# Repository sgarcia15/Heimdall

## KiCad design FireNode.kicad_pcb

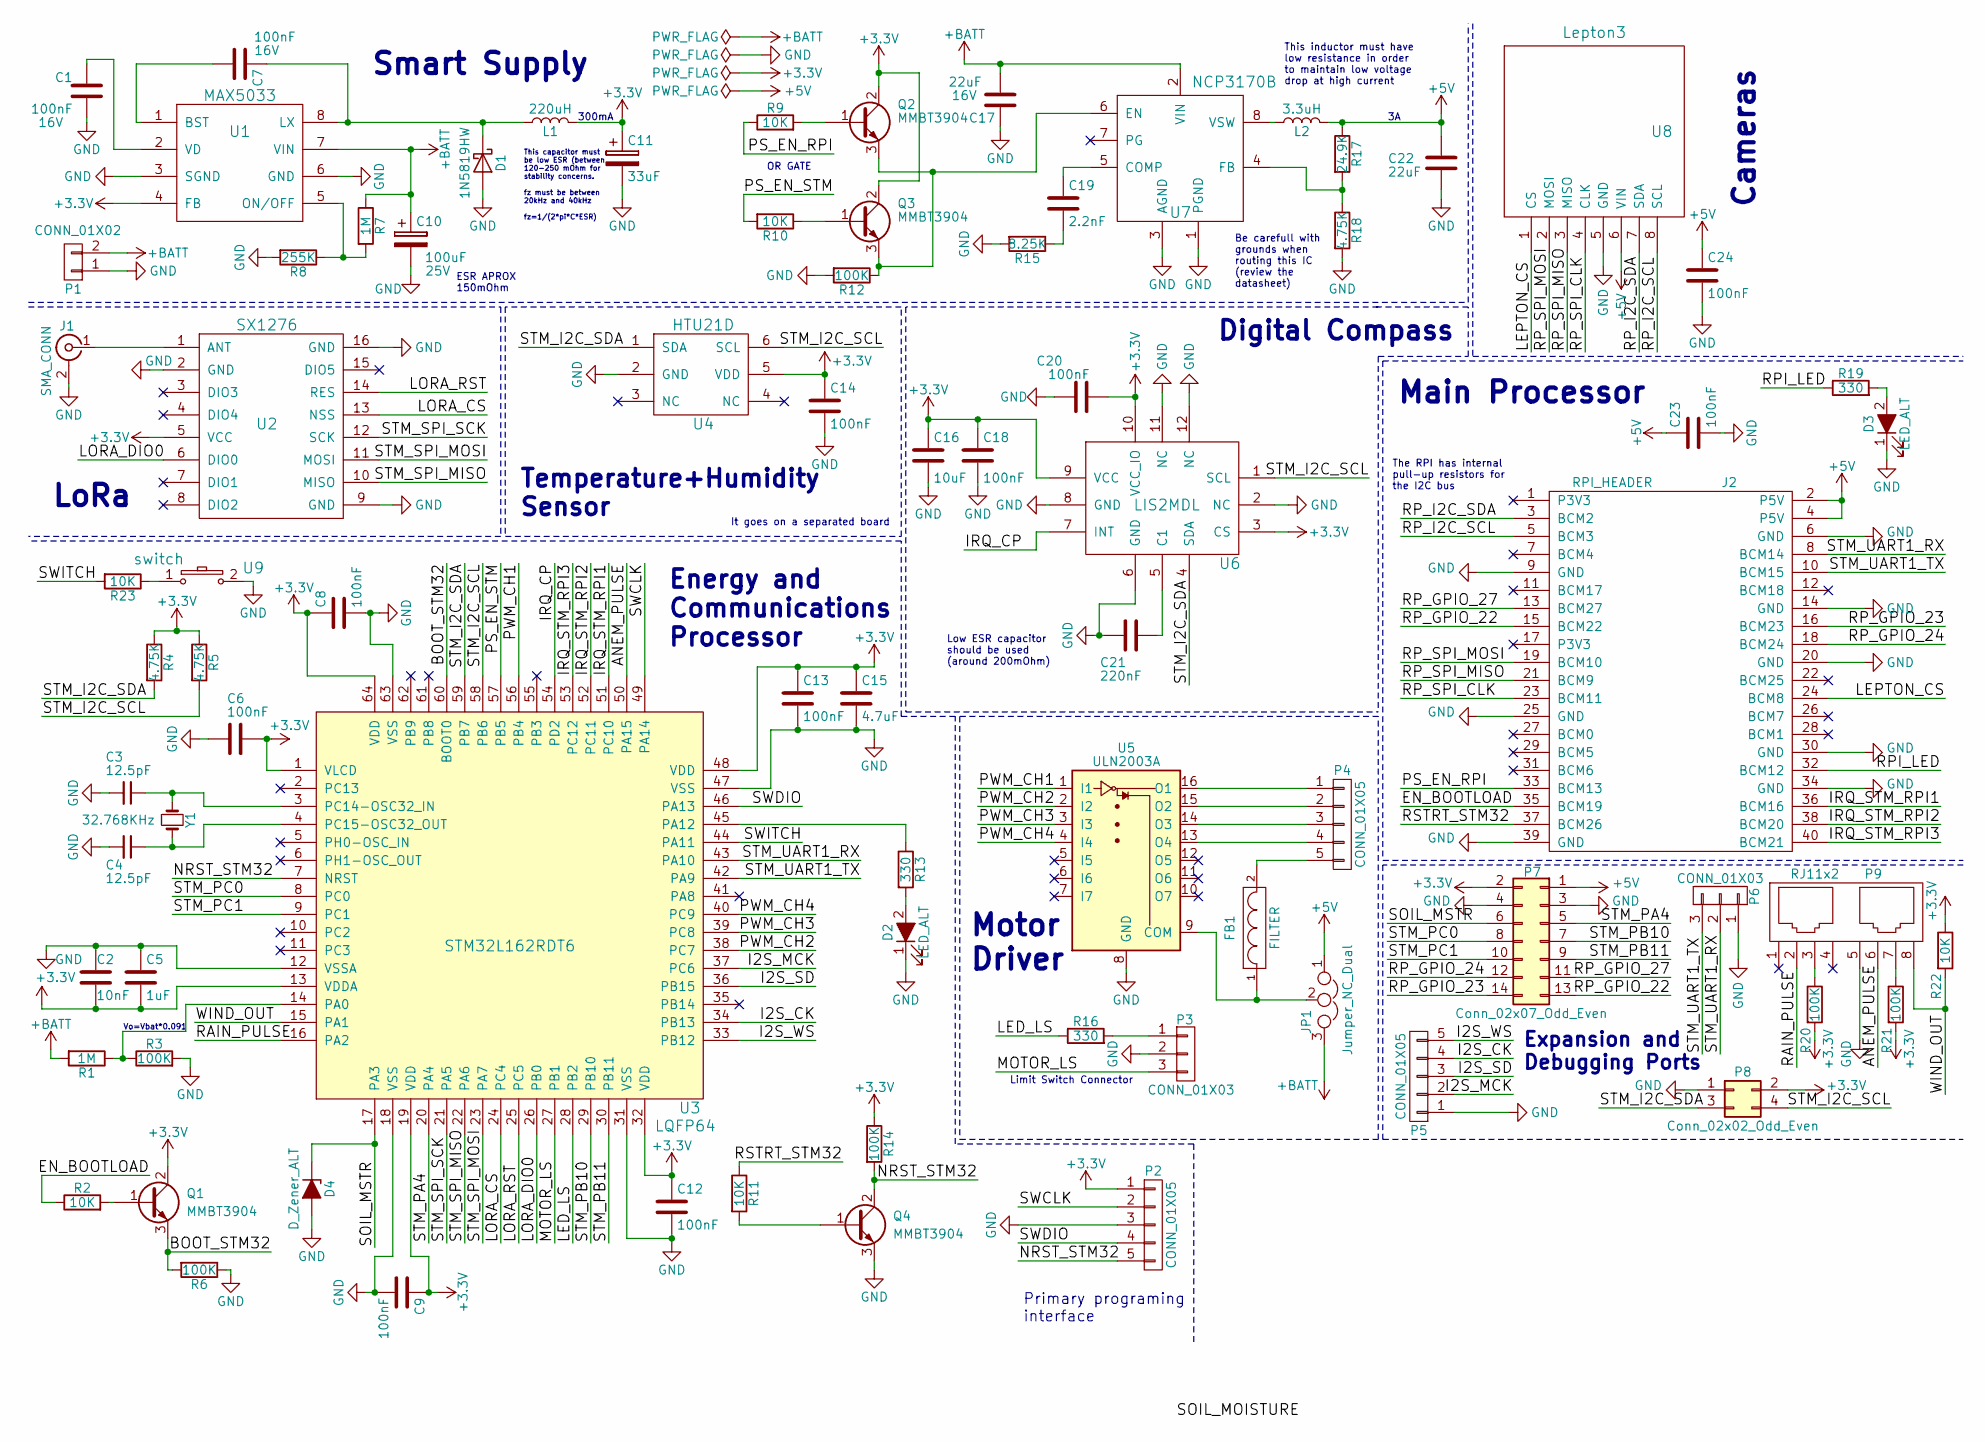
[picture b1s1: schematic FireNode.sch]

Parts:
C1, C6, C7, C8, C9, C12, C13, C14, C18, C20, C23, C24: 100nF; C_0603
C2: 10nF; C_0603
C3, C4: 12.5pF; C_0603
C5: 1uF; C_0603
C10: 100uF; CP_Elec_6.3x7.7
C11: 33uF; CP_Elec_6.3x5.8
C15: 4.7uF; C_0603
C16: 10uF; C_0603
C17, C22: 22uF; C_0805
C19: 2.2nF; C_0805
C21: 220nF; C_0603
D1: 1N5819HW; D_SOD-123
D2, D3: LED_ALT; LED_0805
D4: D_Zener_ALT; D_SOD-123
FB1: FILTER; L_0603
J1: SMA_CONN; SMA-SMD
J2: RPI_HEADER; Socket_Strip_Straight_2x20_Pitch2.54mm
JP1: Jumper_NC_Dual; SMD-JUMPER
L1: 220uH; IND_6,20X5,25
L2: 3.3uH; IND-6.5mm
P1: CONN_01X02; CONN-5mm
P2, P5: CONN_01X05; Pin_Header_Straight_1x05_Pitch2.54mm
P3, P6: CONN_01X03; Pin_Header_Straight_1x03_Pitch2.54mm
P4: CONN_01X05; CONN-MOT-5
P7: Conn_02x07_Odd_Even; Socket_Strip_Straight_2x07_Pitch2.54mm
P8: Conn_02x02_Odd_Even; Pin_Header_Straight_2x02_Pitch2.54mm
P9: RJ11x2; 2xRJ11
Q1, Q2, Q3, Q4: MMBT3904; SOT-23
R1, R7: 1M; R_0603
R2, R9, R10, R11, R22, R23: 10K; R_0603
R3, R6, R12, R14, R20, R21: 100K; R_0603
R4, R5, R18: 4.75K; R_0603
R8: 255K; R_0603
R13, R16, R19: 330; R_0603
R15: 8.25K; R_0603
R17: 24.9K; R_0603
U1: MAX5033; SOIC-8-N
U2: SX1276
U3: STM32L162RDT6; LQFP-64_10x10mm_Pitch0.5mm
U4: HTU21D
U5: ULN2003A; SOIC-16_3.9x9.9mm_Pitch1.27mm
U6: LIS2MDL; LGA-12_2x2mm_Pitch0.5mm
U7: NCP3170B; SOIC-8-N
U8: Lepton3; Pin_Header_Straight_1x08_Pitch2.54mm
U9: switch; SW_SPST_EVPBF
Y1: 32.768KHz; Crystal_C38-LF_d3.0mm_l8.0mm_Horizontal

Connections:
+3V3: C2.2, C5.2, C6.1, C8.1, C9.1, C11.1, C12.1, C13.1, C14.1, C15.1, C16.1, C18.1, C20.2, L1.2, P2.1, P7.2, P8.2, Q1.2 (C), Q2.2 (C), Q3.2 (C), R4.1, R5.1, R14.1, R20.2, R21.2, R22.1, U1.4 (FB), U2.5 (VCC), U3.1 (VLCD), U3.13 (VDDA), U3.19 (VDD), U3.32 (VDD), U3.48 (VDD), U3.64 (VDD), U4.5 (VDD), U6.3 (CS), U6.9 (VCC), U6.10 (VCC_IO)
+5V: C22.1, C23.1, C24.1, J2.2 (P5V), J2.4 (P5V), JP1.1, L2.2, P7.1, R17.1, U8.6 (VIN)
+BATT: C10.1, C17.2, JP1.3, P1.2, R1.2, R7.1, U1.7 (VIN), U7.2 (VIN)
/ANEM_PULSE: P9.6, U3.50 (PA15)
/BOOT_STM32: Q1.3 (E), R6.2, U3.60 (BOOT0)
/EN_BOOTLOAD: J2.35 (BCM19), R2.1
/I2S_CK: P5.4, U3.34 (PB13)
/I2S_MCK: P5.2, U3.37 (PC6)
/I2S_SD: P5.3, U3.36 (PB15)
/I2S_WS: P5.5, U3.33 (PB12)
/IRQ_CP: U3.54 (PD2), U6.7 (INT)
/IRQ_STM_RPI1: J2.36 (BCM16), U3.51 (PC10)
/IRQ_STM_RPI2: J2.38 (BCM20), U3.52 (PC11)
/IRQ_STM_RPI3: J2.40 (BCM21), U3.53 (PC12)
/LED_LS: R16.1, U3.28 (PB2)
/LEPTON_CS: J2.24 (BCM8), U8.1 (CS)
/LORA_CS: U2.13 (NSS), U3.24 (PC4)
/LORA_DIO0: U2.6 (DIO0), U3.26 (PB0)
/LORA_RST: U2.14 (RES), U3.25 (PC5)
/MOTOR_LS: P3.3 (P2), U3.27 (PB1)
/NRST_STM32: P2.5, Q4.2 (C), R14.2, U3.7 (NRST)
/PS_EN_RPI: J2.33 (BCM13), R9.1
/PS_EN_STM: R10.2, U3.57 (PB5)
/PWM_CH1: U3.56 (PB4), U5.1 (I1)
/PWM_CH2: U3.38 (PC7), U5.2 (I2)
/PWM_CH3: U3.39 (PC8), U5.3 (I3)
/PWM_CH4: U3.40 (PC9), U5.4 (I4)
/RAIN_PULSE: P9.2, U3.16 (PA2)
/RPI_LED: J2.32 (BCM12), R19.1
/RP_GPIO_22: J2.15 (BCM22), P7.13
/RP_GPIO_23: J2.16 (BCM23), P7.14
/RP_GPIO_24: J2.18 (BCM24), P7.12
/RP_GPIO_27: J2.13 (BCM27), P7.11
/RP_I2C_SCL: J2.5 (BCM3), U8.8 (SCL)
/RP_I2C_SDA: J2.3 (BCM2), U8.7 (SDA)
/RP_SPI_CLK: J2.23 (BCM11), U8.4 (CLK)
/RP_SPI_MISO: J2.21 (BCM9), U8.3 (MISO)
/RP_SPI_MOSI: J2.19 (BCM10), U8.2 (MOSI)
/RSTRT_STM32: J2.37 (BCM26), R11.1
/SOIL_MSTR: D4.1 (K), P7.6, U3.17 (PA3)
/STM_I2C_SCL: P8.4, R5.2, U3.58 (PB6), U4.6 (SCL), U6.1 (SCL)
/STM_I2C_SDA: P8.3, R4.2, U3.59 (PB7), U4.1 (SDA), U6.4 (SDA)
/STM_PA4: P7.5, U3.20 (PA4)
/STM_PB10: P7.7, U3.29 (PB10)
/STM_PB11: P7.9, U3.30 (PB11)
/STM_PC0: P7.8, U3.8 (PC0)
/STM_PC1: P7.10, U3.9 (PC1)
/STM_SPI_MISO: U2.10 (MISO), U3.22 (PA6)
/STM_SPI_MOSI: U2.11 (MOSI), U3.23 (PA7)
/STM_SPI_SCK: U2.12 (SCK), U3.21 (PA5)
/STM_UART1_RX: J2.8 (BCM14), P6.2 (P1), U3.43 (PA10)
/STM_UART1_TX: J2.10 (BCM15), P6.3 (P2), U3.42 (PA9)
/SWCLK: P2.2, U3.49 (PA14)
/SWDIO: P2.4, U3.46 (PA13)
/SWITCH: R23.2, U3.44 (PA11)
/WIND_OUT: P9.8, R22.2, U3.15 (PA1)
GND: C1.1, C2.1, C3.2, C4.2, C5.1, C6.2, C8.2, C9.2, C10.2, C11.2, C12.2, C13.2, C14.2, C15.2, C16.2, C17.1, C18.2, C20.1, C21.2, C22.2, C23.2, C24.2, D1.2 (A), D2.1 (K), D3.1 (K), D4.2 (A), J1.2 (Ext), J2.6 (GND), J2.9 (GND), J2.14 (GND), J2.20 (GND), J2.25 (GND), J2.30 (GND), J2.34 (GND), J2.39 (GND), P1.1, P2.3, P3.2 (P1), P5.1, P6.1, P7.3, P7.4, P8.1, P9.5, Q4.3 (E), R3.2, R6.1, R8.2, R12.2, R15.2, R18.2, U1.3 (SGND), U1.6 (GND), U2.2 (GND), U2.9 (GND), U2.16 (GND), U3.12 (VSSA), U3.18 (VSS), U3.31 (VSS), U3.47 (VSS), U3.63 (VSS), U4.2 (GND), U5.8 (GND), U6.2 (NC), U6.6 (GND), U6.8 (GND), U6.11 (NC), U6.12 (NC), U7.1 (PGND), U7.3 (AGND), U8.5 (GND), U9.2
unnamed: C1.2, U1.2 (VD)
unnamed: C3.1, U3.3 (PC14-OSC32_IN), Y1.1
unnamed: C4.1, U3.4 (PC15-OSC32_OUT), Y1.2
unnamed: C7.1, D1.1 (K), L1.1, U1.8 (LX)
unnamed: C7.2, U1.1 (BST)
unnamed: C19.1, U7.5 (COMP)
unnamed: C19.2, R15.1
unnamed: C21.1, U6.5 (C1)
unnamed: D2.2 (A), R13.2
unnamed: D3.2 (A), R19.2
unnamed: FB1.1, JP1.2, U5.9 (COM)
unnamed: FB1.2, P4.5
unnamed: J1.1 (In), U2.1 (ANT)
unnamed: L2.1, U7.8 (VSW)
unnamed: P3.1, R16.2
unnamed: P4.1, U5.16 (O1)
unnamed: P4.2, U5.15 (O2)
unnamed: P4.3, U5.14 (O3)
unnamed: P4.4, U5.13 (O4)
unnamed: P9.3, R20.1
unnamed: P9.7, R21.1
unnamed: Q1.1 (B), R2.2
unnamed: Q2.1 (B), R9.2
unnamed: Q2.3 (E), Q3.3 (E), R12.1, U7.6 (EN)
unnamed: Q3.1 (B), R10.1
unnamed: Q4.1 (B), R11.2
unnamed: R1.1, R3.1, U3.14 (PA0)
unnamed: R7.2, R8.1, U1.5 (ON/OFF)
unnamed: R13.1, U3.45 (PA12)
unnamed: R17.2, R18.1, U7.4 (FB)
unnamed: R23.1, U9.1

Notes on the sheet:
ESR APROX 150mOhm
This capacitor must be low ESR (between 120-250 mOhm for stability concerns. fz must be between 20kHz and 40kHz fz=1/(2*pi*C*ESR)
Low ESR capacitor should be used (around 200mOhm)
The RPI has internal pull-up resistors for the I2C bus
Be carefull with grounds when routing this IC (review the datasheet)
Primary programing interface
Smart Supply
Cameras
Main Processor
Vo=Vbat*0.091
LoRa
Temperature+Humidity Sensor
Digital Compass
Expansion and Debugging Ports
Motor Driver
Limit Switch Connector
Energy and Communications Processor
This inductor must have low resistance in order to maintain low voltage drop at high current
It goes on a separated board
300mA
OR GATE

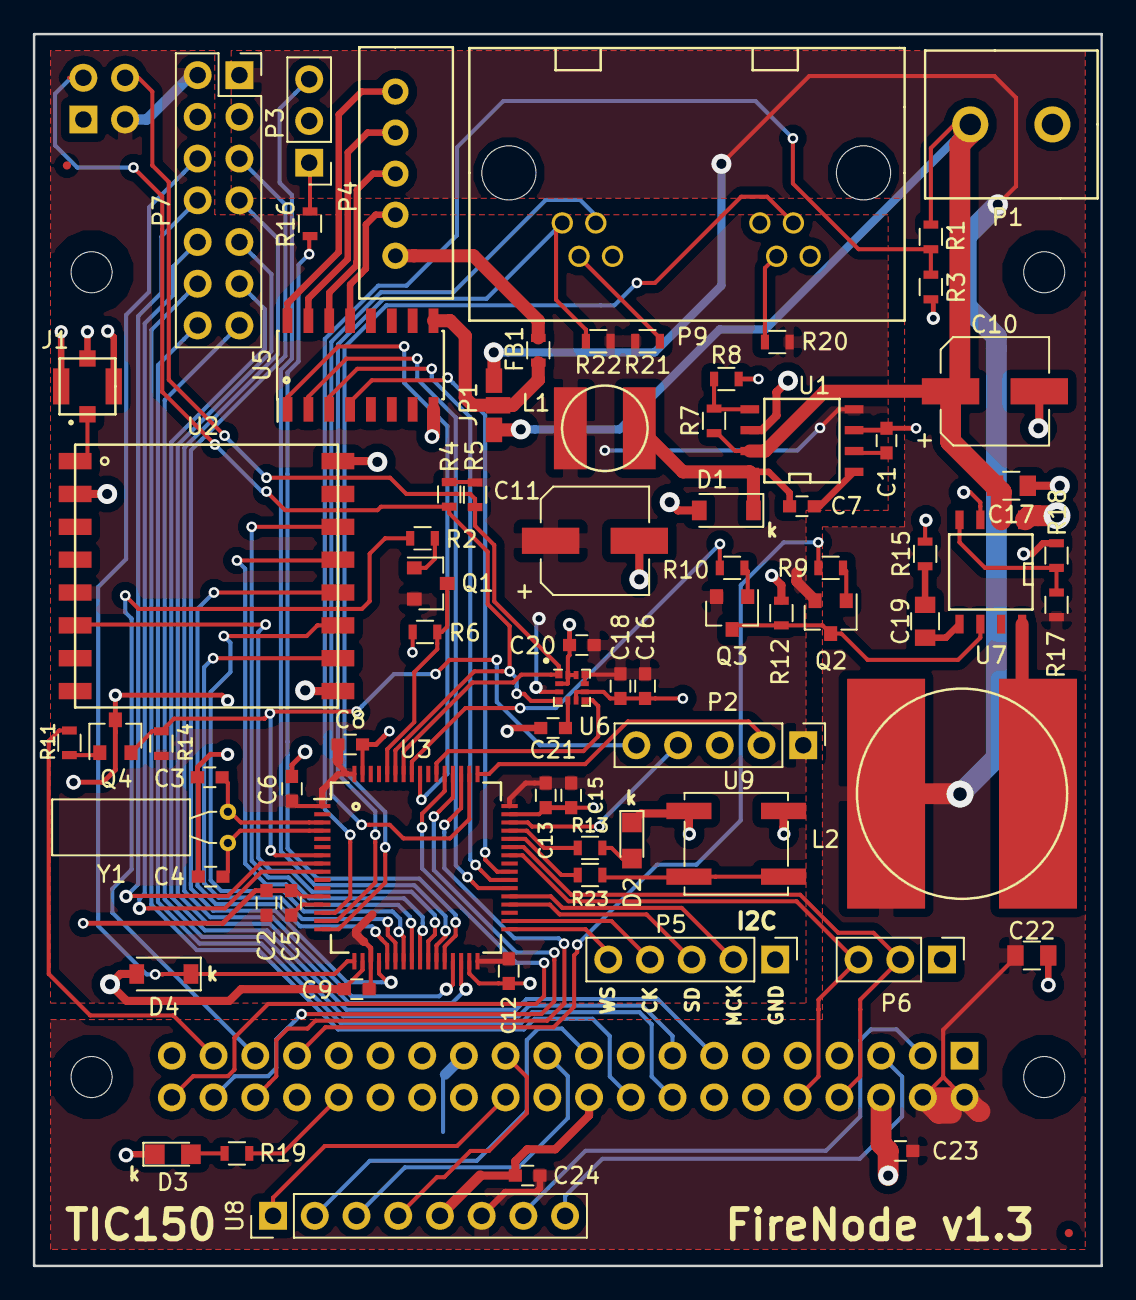
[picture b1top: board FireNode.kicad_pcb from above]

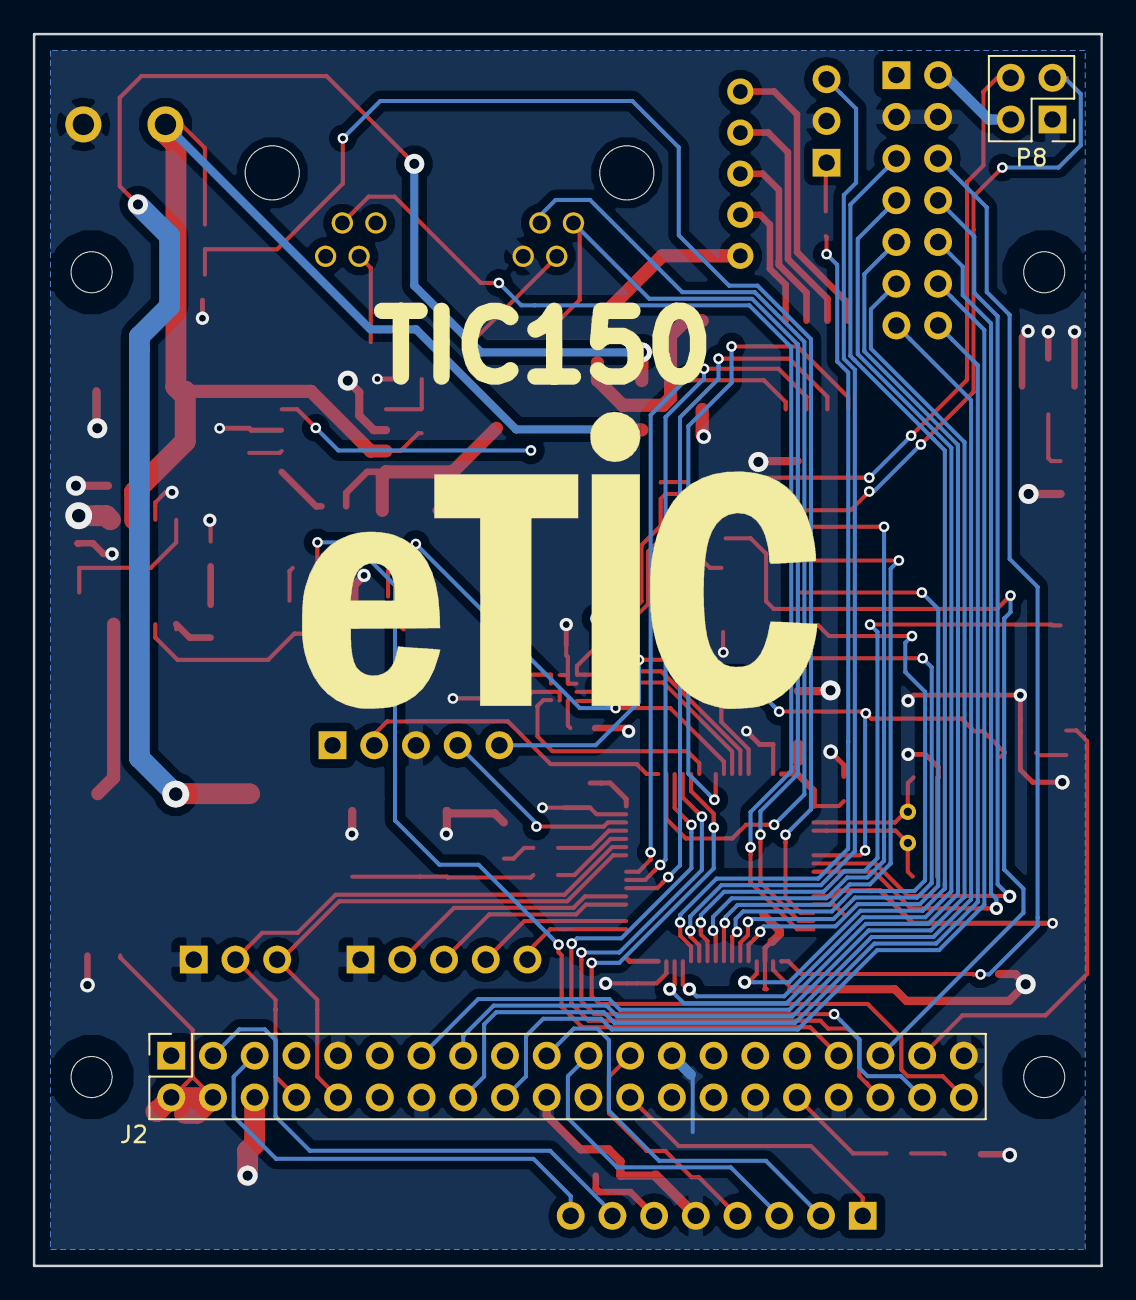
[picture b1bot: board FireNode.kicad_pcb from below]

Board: 2 copper layers, 65.0 x 75.0 mm, 78 parts (2 on the bottom side), 88 nets.
